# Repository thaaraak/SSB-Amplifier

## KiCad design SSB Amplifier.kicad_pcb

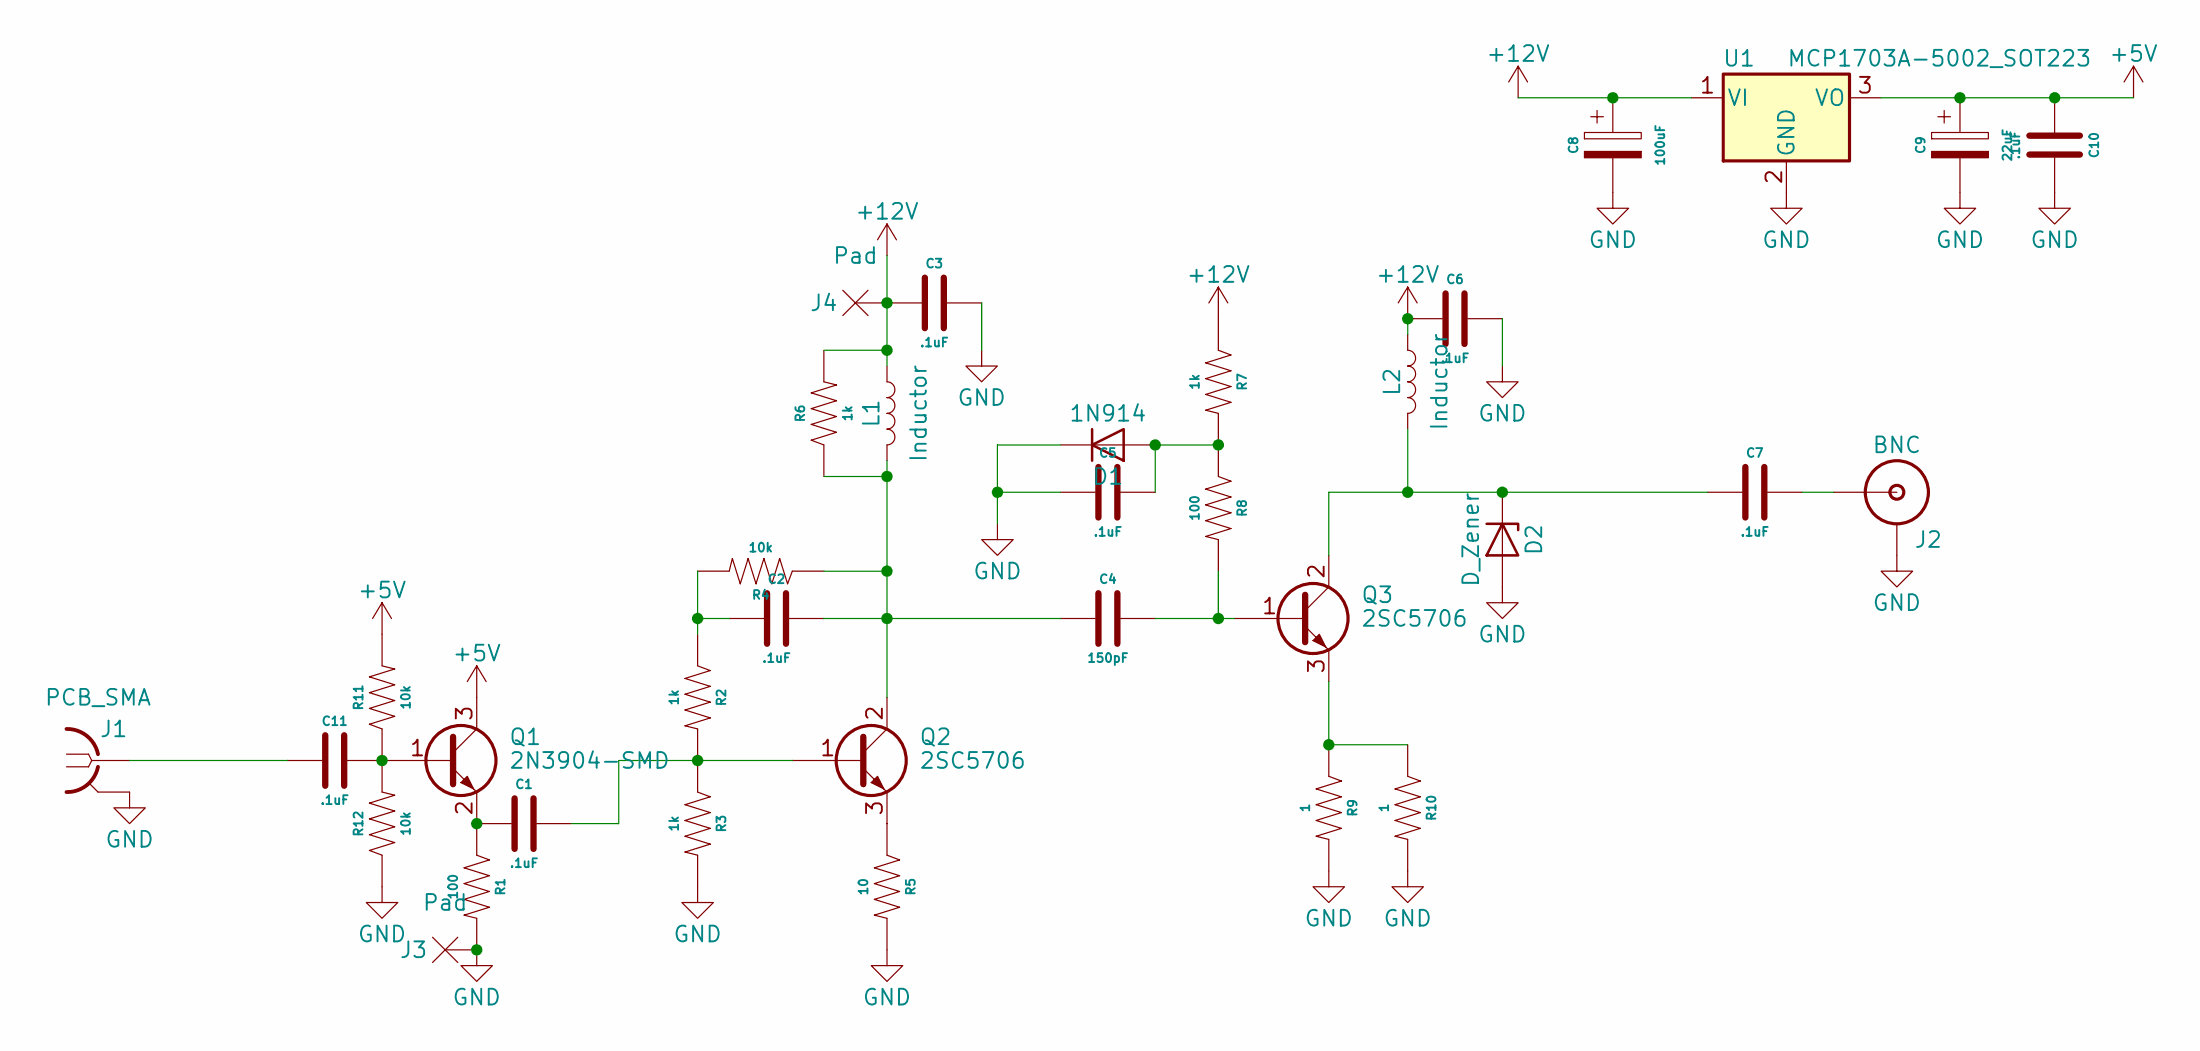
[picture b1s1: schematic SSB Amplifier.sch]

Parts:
C1, C2, C3, C5, C6, C7, C10, C11: .1uF; Capacitor 0805
C4: 150pF; Capacitor 0805
C8: 100uF; CP_Elec_6.3x5.4
C9: 22uF; CP_Elec_4x5.4
D1: 1N914; D_SOD-323_HandSoldering
D2: D_Zener; D_A-405_P10.16mm_Horizontal
J1: PCB_SMA; PCB SMA
J2: BNC
J3, J4: Pad
L1: Inductor; T37_Inductor
L2: Inductor; T50_Inductor
Q1: 2N3904-SMD; SOT-23
Q2, Q3: 2SC5706; TO-251-3_Vertical
R1, R8: 100; Resistor 0805
R2, R3, R6, R7: 1k; Resistor 0805
R4, R11, R12: 10k; Resistor 0805
R5: 10; Resistor 0805
R9, R10: 1; R_Axial_DIN0204_L3.6mm_D1.6mm_P2.54mm_Vertical
U1: MCP1703A-5002_SOT223; TO-252-3_TabPin2

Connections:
+5V: C9.1, C10.1, Q1.3 (C), R11.2, U1.3 (VO)
+12V: C3.1, C6.1, C8.1, J4.1, L1.1, L2.1, R6.2, R7.1, U1.1 (VI)
GND: C3.2, C5.2, C6.2, C8.2, C9.2, C10.2, D1.1 (K), D2.2 (A), J1.2, J1.3 (2), J1.4 (2), J1.5 (2), J2.GND, J3.1, R1.2, R3.2, R5.2, R9.2, R10.2, R12.1, U1.2 (GND)
unnamed: C1.1, Q1.2 (E), R1.1
unnamed: C1.2, Q2.1 (B), R2.2, R3.1
unnamed: C2.1, R2.1, R4.2
unnamed: C2.2, C4.1, L1.2, Q2.2 (C), R4.1, R6.1
unnamed: C4.2, Q3.1 (B), R8.2
unnamed: C5.1, D1.2 (A), R7.2, R8.1
unnamed: C7.1, D2.1 (K), L2.2, Q3.2 (C)
unnamed: C7.2, J2.S (OUT)
unnamed: C11.1, J1.1
unnamed: C11.2, Q1.1 (B), R11.1, R12.2
unnamed: Q2.3 (E), R5.1
unnamed: Q3.3 (E), R9.1, R10.1

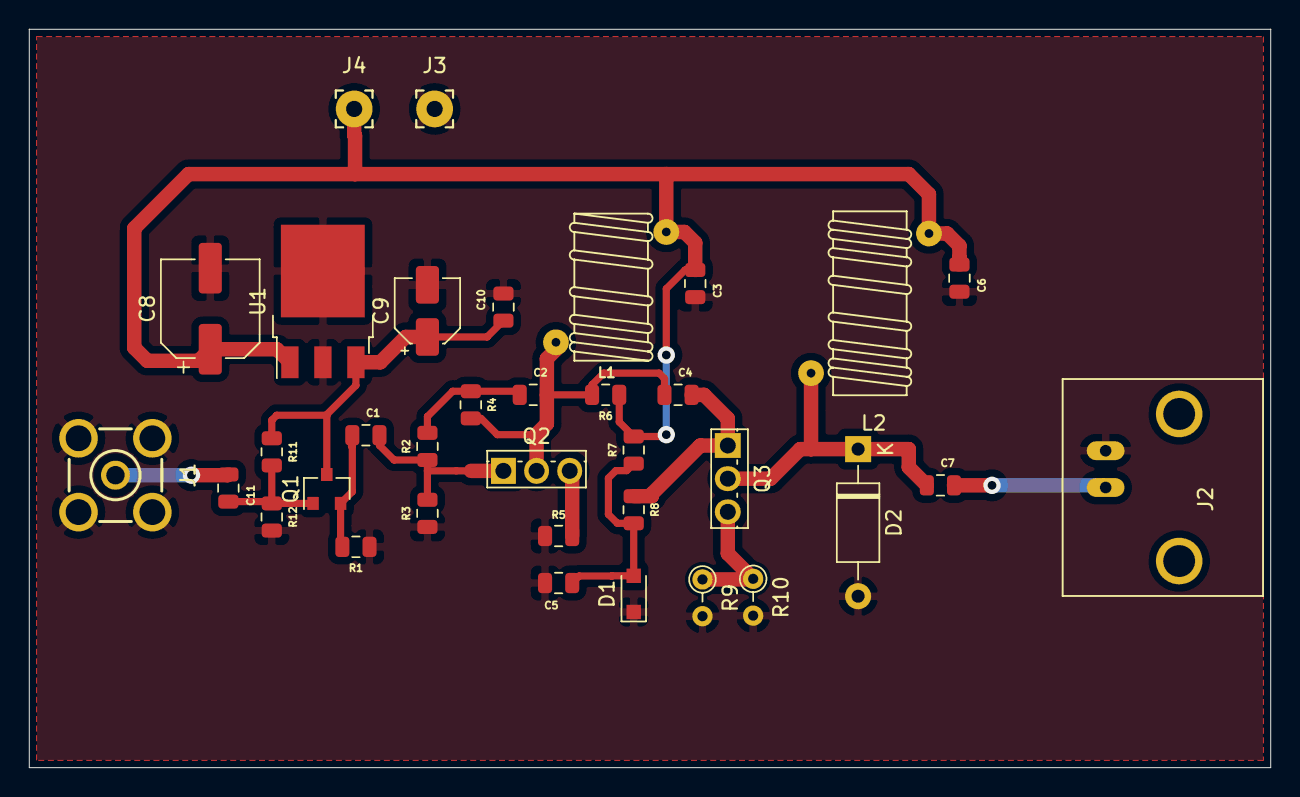
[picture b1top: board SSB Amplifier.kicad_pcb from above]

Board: 2 copper layers, 85.8 x 51.0 mm, 35 parts (0 on the bottom side), 15 nets.
